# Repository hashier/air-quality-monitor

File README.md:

# air-quality-monitor

DIY air quality monitor on an ESP32-C6, running ESPHome and reporting to Home Assistant.

## Hardware

- **ESP32-C6** dev board (`esp32-c6-devkitc-1`)
- **Sensirion SCD40**: CO2, temperature, humidity (I2C `0x62`)
- **Sensirion SPS30**: particulate matter PM1.0 / 2.5 / 4.0 / 10.0 (I2C `0x69`, 5V)
- **SSD1306** 128x64 OLED (I2C `0x3C`)
- **WS2812** RGB LED (GPIO8)

All three sensors share one I2C bus at 100 kHz (the SPS30 datasheet ceiling).

## Repo layout

- `esphome/`: firmware (ESPHome config + secrets template)
- `kicad/`: custom PCB (planned)
- `case/`: 3D-printed enclosure (planned)

## Firmware

```fish
cd esphome
cp secrets.yaml.example secrets.yaml   # then fill in real values
esphome run air-quality-monitor.yaml
```

`secrets.yaml` holds WiFi / API / OTA credentials and is gitignored. Never commit it.

## Notes

- **SCD40 auto-recovery:** the sensor can get knocked out of periodic measurement (a flaky power connection resets it). A YAML watchdog detects CO2 going stale and re-inits it over raw I2C (stop, then start). Two Home Assistant diagnostics track this: `CO2 Stall Count` and `CO2 Currently Stalled`.
- **Temperature offset** (`6.5C`) is a provisional self-heating correction for the breadboard build. Re-tune in the final enclosure by comparing side by side against a reference.
- **Warm-up filters** drop the SCD40 startup transient (temperature/humidity 5 min, CO2 30 s).

## Status

Work in progress: currently on a breadboard. Custom PCB and enclosure are next.

## To test

- **Separate 3.3V regulator for the SCD40:** power it from 5V through its own LDO (AP2112K-3.3, 1 µF on input and output, EN tied to VIN) instead of the ESP32 board's 3V3 pin. Sensirion's SCD4x datasheet recommends a separate LDO and allows at most 30 mV supply ripple, and the SCD40 peaks at 205 mA while the ESP32's WiFi bursts share the same regulator. Compare `CO2 Stall Count` before and after.
- **Everything on one I2C bus:** SCD40, OLED and SPS30 together, with the SPS30 on a cable as long as the case needs. Each breakout brings its own pull-ups, so check whether the bus still works with all of them in parallel, and whether the SPS30 needs extra ones.

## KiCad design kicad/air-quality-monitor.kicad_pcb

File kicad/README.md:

# kicad

Custom PCB design (KiCad) for the air quality monitor. Planned.

Target layout: thermal zoning so the SCD40 sits away from the ESP32 and
regulator heat and the SPS30 exhaust, on a slot-isolated peninsula, with the
SPS30 airflow ducted to separate case vents. See the project notes for details.

## v1 design (draft, untested)

**Untested.** Nothing below has been built yet. Parts of it depend on the
breadboard tests in the main README's "To test" section, and change if a test
says so.

One PCB for every build, ordered in a batch of 5 and hand-soldered (through-hole
where possible, no assembly service). Each build gets its own 3D-printed case:

| Build | SCD40 | OLED | SPS30 |
|---|---|---|---|
| Living room | yes | yes | yes |
| Bedroom | yes | no | no |
| Portable (power bank, car) | yes | yes | no |

Home Assistant is the control plane, so there are no buttons or buzzers. Unused
dev board pins keep their holes for wiring something on later. Battery power is
for a later version.

### Power

- **Input:** a USB-C breakout board (AliExpress 1005004848153846, 20.2 x 14 mm)
  on an 8-pin 2.54 mm header, 5V, no USB PD. Only VBUS and GND are wired. The
  board has its own 5.1 kΩ resistors on CC1 and CC2, so a USB-C charger turns
  on 5V. Pin order and screw holes still need checking on the real board.
- **5V rail** feeds the SPS30 and both 3.3V regulators directly.
- **Dev board 5V pin** (J1 pin 14) is fed from the 5V rail through a Schottky
  diode, which a jumper cap bypasses by default (see below). With the cap
  pulled, plugging in the dev board's own USB at the same time can't push
  current back into the PCB's USB-C. In Espressif's DevKitC-1 schematic v1.4,
  each USB port reaches `VCC_5V` through a 1N5819, and `VCC_5V` is the 5V pin
  with no diode in between.
- **Two AP2112K-3.3** (SOT-23-5) from the 5V rail, each with EN tied to VIN and
  1 µF on input and output, instead of the dev board's 3V3, which also feeds the
  WiFi:
  - **3V3_SCD** feeds only the SCD40. Pending the LDO test.
  - **3V3_AUX** feeds the OLED and the two JST ZH sensor sockets.
- **Fallback to the dev board's rails:**
  - each 3.3V rail can be switched to the dev board's 3V3 pin with a 3-pad
    solder jumper (`SolderJumper_3_Bridged12`): a thin trace joins the LDO side
    from the factory, so the board works without soldering a jumper; to switch,
    cut it and put a solder blob on the dev board side. Solder jumpers,
    not pin headers with caps, because a push-fit contact in the SCD40's supply
    is the kind of fault behind the earlier stalls;
  - a 2-pin header with a jumper cap (`Jumper_2_Bridged`) across the Schottky
    diode, cap on by default: the dev board gets the full 5V, not 5V minus the
    diode drop, likely too little for its AMS1117 (an ESP32-S3 board went into
    a brownout loop at 4.9V on its 5V pin). A loose cap only puts the diode back
    in the path. Pull the cap before plugging in both USB cables, otherwise the
    device on the PCB's USB-C gets fed backwards. With the cap on, the dev board's
    own USB also powers the whole PCB;
  - two optional electrolytics (C6 100µF, C7 470µF, not fitted) on the dev
    board's 3V3 pin: that pair (570µF) stopped the same S3 board's brownout loop
    at 5.0V.

### Dev board

ESP32-C6-DevKitC-1 or a pin-compatible copy, soldered through its pin headers:
2 rows of 16 pins at 2.54 mm, rows 22.86 mm apart, board 25.4 × 51.8 mm
(Espressif dimension drawing v1.2). Pin 16 on both rows stays unconnected:
it is NC on Espressif's board and GND on the QSZNTEC copy.

Every header hole the PCB connects to (5V, 3V3, SDA, SCL, and GND on two pins
with one jumper each) goes through a cuttable solder jumper
(`SolderJumper_2_Bridged` in KiCad's `Jumper` library), so another board's pin
in that position is never shorted to anything. A board with a
different pinout fits by cutting the jumper and wiring its pin to the jumper's
pad. This does not fix a different row distance.

I2C stays on the pins the firmware uses today: SDA GPIO21, SCL GPIO22, at
100 kHz (the SPS30 maximum).

### Sensors and display

- **SCD40:** the breakout (pins SDA, SCL, VDD, GND; it already has its own
  pull-ups R1/R2 and C1), soldered on permanently through its pin header. Far
  from the dev board, both AP2112Ks and the SPS30 exhaust.
- **OLED:** 4 holes at the board edge in the module's order GND, VDD, SCK, SDA.
  Solder the module straight in, run wires to place it elsewhere in a case, or
  leave it out. No copper or parts under the module.
- **SPS30 (optional):** JST ZH 5-pin socket (B5B-ZR) for its ZHR-5 cable. Pins
  per the SPS30 datasheet v2.0: 1 VDD (5V, 4.5 to 5.5V), 2 SDA, 3 SCL, 4 SEL,
  5 GND. SEL goes to GND to select I2C. Up to 80 mA during fan start. Sensirion
  recommends UART over I2C for cables longer than 20 cm.
- **Sensor sockets (1 or 2):** for trying out other I2C sensors (the ENS160 and
  AHT21 module, for example), each soldered to a ZH cable. JST ZH 4-pin,
  1.5 mm pitch, through-hole (B4B-ZR), pin order GND, 3.3V, SDA, SCL as in
  SparkFun's Qwiic. Not Qwiic plugs: Qwiic uses the smaller surface-mount
  JST SH (1 mm pitch), too fine to solder by hand here.

### Still open

- Pull-ups: the SCD40 breakout and probably the OLED module bring their own,
  and the SPS30 needs some on the bus. Whether the PCB adds pull-ups is
  decided by the bus test.
- Exact Schottky diode and capacitor parts, picked with the footprints.
  C1 to C5 have 4 holes, for leads 2.5 mm or 5 mm apart, until the
  capacitors at hand are measured. C1 (10 µF) has an electrolytic footprint
  with a + mark, which also takes a ceramic one.
- ESP32-S3 dev board (2 × 22 pins from a photo, rows 25.4 mm apart: measured
  about 25 mm with a folding ruler) is not supported in v1.

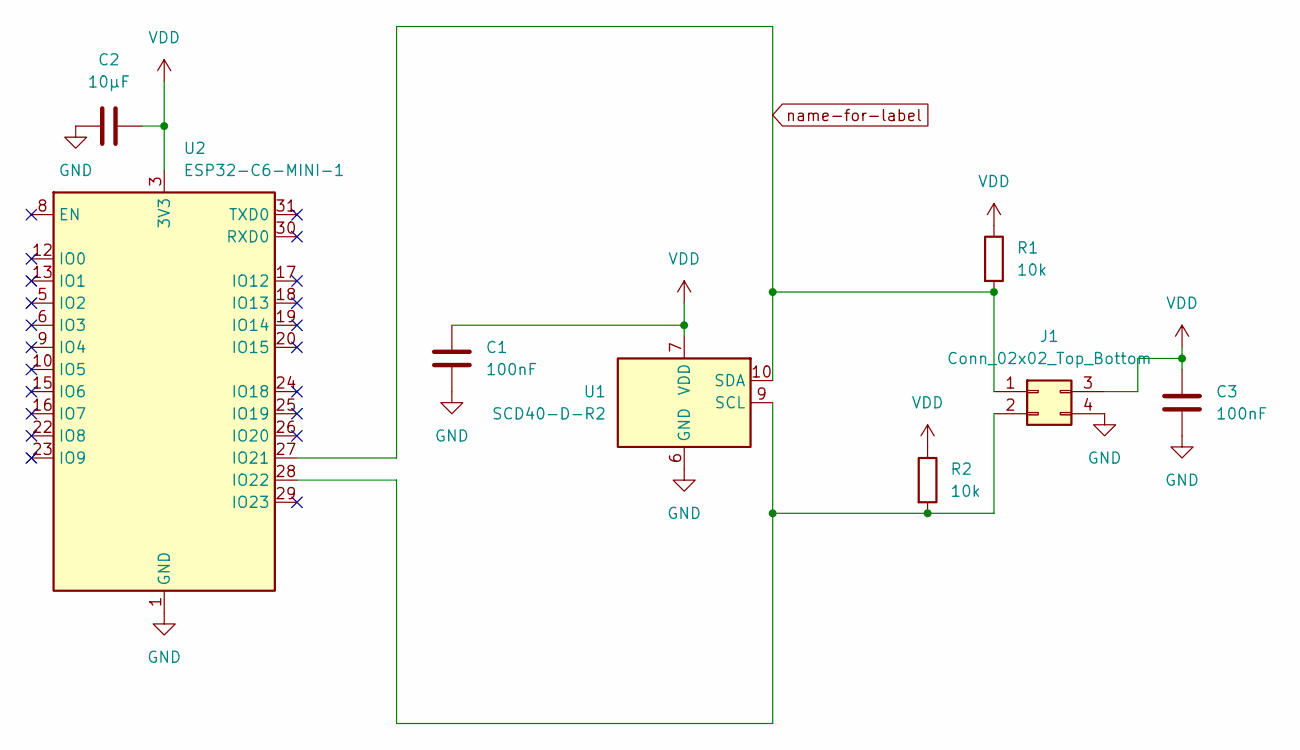
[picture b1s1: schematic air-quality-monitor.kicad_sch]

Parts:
C1, C3: 100nF; C_0603_1608Metric_Pad1.08x0.95mm_HandSolder
C2: 10µF; C_0603_1608Metric_Pad1.08x0.95mm_HandSolder
J1: Conn_02x02_Top_Bottom; PinHeader_2x02_P2.54mm_Vertical
R1, R2: 10k; R_0603_1608Metric_Pad0.98x0.95mm_HandSolder
U1: SCD40-D-R2; Sensirion_SCD4x-1EP_10.1x10.1mm_P1.25mm_EP4.8x4.8mm
U2: ESP32-C6-MINI-1

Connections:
GND: C1.2, C2.2, C3.2, J1.4, U1.6 (GND), U1.20 (GND), U1.21 (GND), U2.1 (GND), U2.2 (GND), U2.11 (GND), U2.14 (GND), U2.36 (GND), U2.37 (GND), U2.38 (GND), U2.39 (GND), U2.40 (GND), U2.41 (GND), U2.42 (GND), U2.43 (GND), U2.44 (GND), U2.45 (GND), U2.46 (GND), U2.47 (GND), U2.48 (GND), U2.49 (GND), U2.50 (GND), U2.51 (GND), U2.52 (GND), U2.53 (GND)
unnamed: J1.2, R2.2, U1.9 (SCL), U2.28 (IO22)
VDD: C1.1, C2.1, C3.1, J1.3, R1.1, R2.1, U1.7 (VDD), U1.19 (VDD), U2.3 (3V3)
name-for-label: J1.1, R1.2, U1.10 (SDA), U2.27 (IO21)

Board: 2 copper layers, 8 parts (0 on the bottom side), 4 nets, no tracks yet.
